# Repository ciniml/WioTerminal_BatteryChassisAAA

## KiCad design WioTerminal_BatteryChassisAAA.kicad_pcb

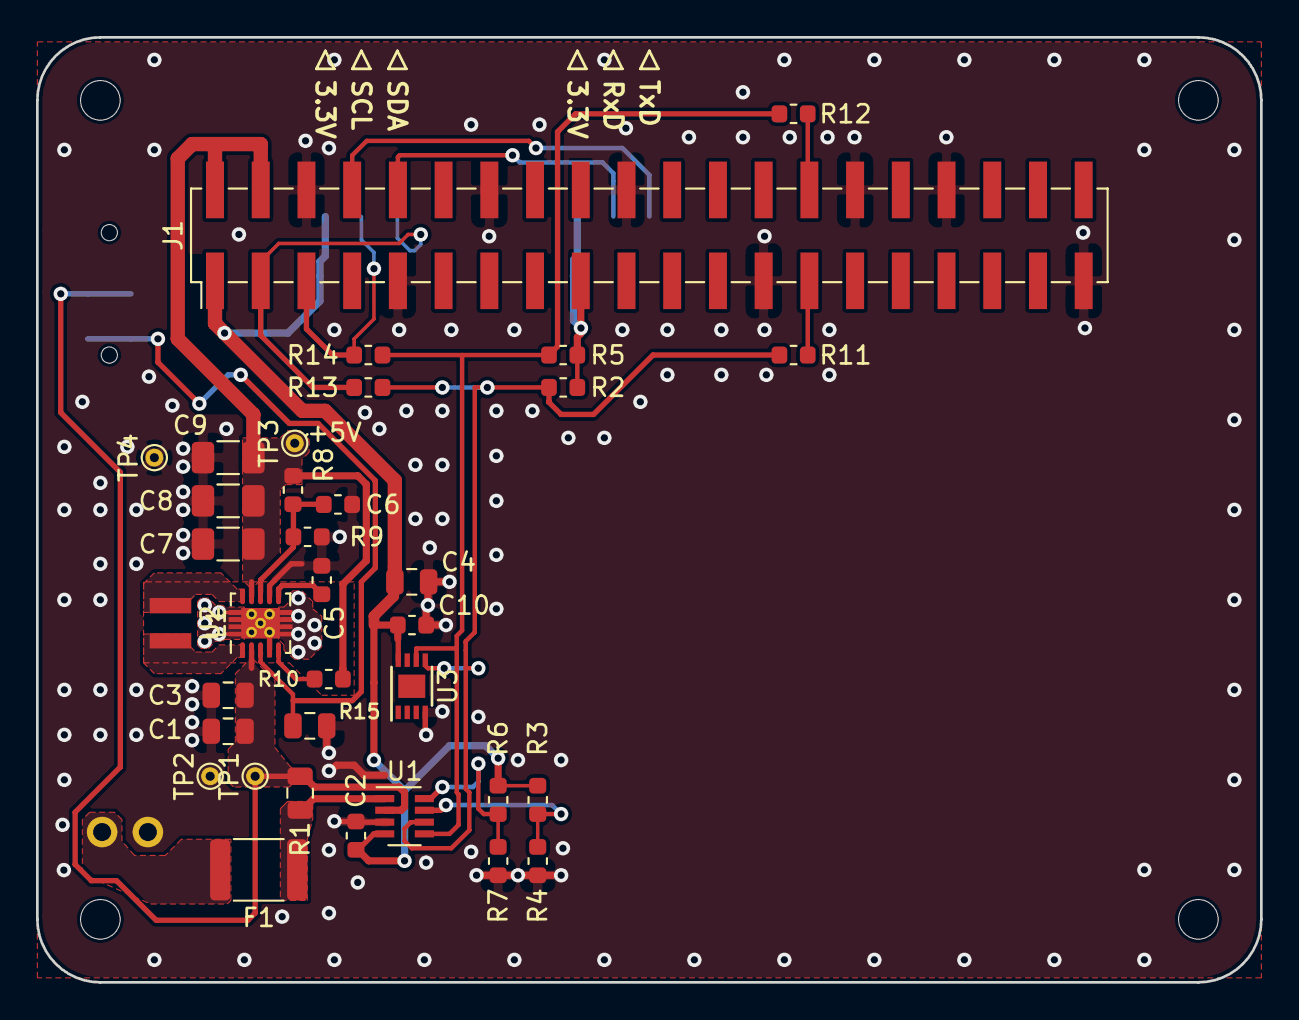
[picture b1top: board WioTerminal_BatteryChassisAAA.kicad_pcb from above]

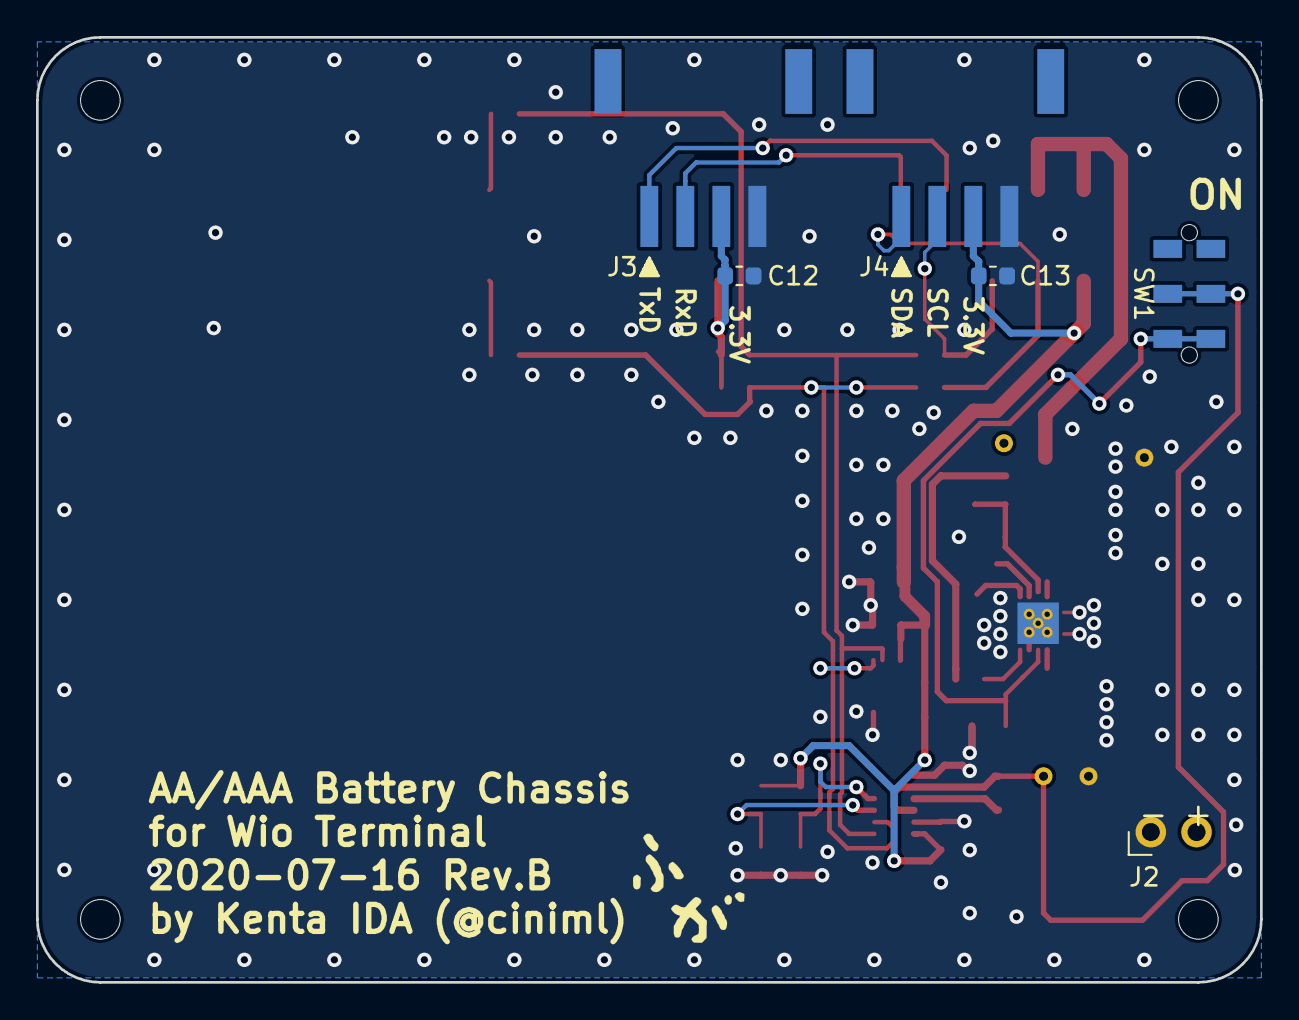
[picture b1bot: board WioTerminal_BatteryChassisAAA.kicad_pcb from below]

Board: 2 copper layers, 68.0 x 52.5 mm, 46 parts (7 on the bottom side), 22 nets.

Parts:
C1, C3, C4: 10u; C_0805_2012Metric
C2, C5, C10: 100n; C_0603_1608Metric
C6: 10p; C_0603_1608Metric
C7, C8, C9: 22u; C_1206_3216Metric
C12, C13: 1u; C_0603_1608Metric
F1: 1A; Fuse_1812_4532Metric
J1: Raspberry_Pi_2_3; PinHeader_2x20_P2.54mm_Vertical_SMD
J2: Ext. BAT; PinHeader_1x02_P2.54mm_Horizontal
J3, J4: GROVE; PHS-4AW
L1: 1u, 2.5A; 74438323010
LOGO1: Logo_Open_Hardware_Small; logo
MH1, MH2, MH3, MH4: Corner; MountingHole_2.2mm_M2_DIN965_Mask
R1: 0.04; R_0805_2012Metric
R2, R5: 4.7k; R_0603_1608Metric
R3, R6, R11, R12: 0; R_0603_1608Metric
R4, R7, R13, R14: DNP; R_0603_1608Metric
R8, R10: 1M; R_0603_1608Metric
R9: 111k; R_0603_1608Metric
R15: 100k; R_0805_2012Metric
SW1: JS102011JAQN
TP1: BAT; TestPoint_THTPad_D1.0mm_Drill0.5mm
TP2: BAT-GND; TestPoint_THTPad_D1.0mm_Drill0.5mm
TP3: +5V; TestPoint_THTPad_D1.0mm_Drill0.5mm
TP4: +5V-GND; TestPoint_THTPad_D1.0mm_Drill0.5mm
U1: INA219; SOT-23-8
U2: TPS63060; Texas_S-PWSON-N10_ThermalVias
U3: ATECC608A; DFN-8-1EP_3x2mm_P0.5mm_EP1.3x1.5mm

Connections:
+3V3: C2.1, C4.1, C10.1, C12.1, C13.1, J1.1, J1.17, J3.3, J4.3, R2.1, R3.1, R5.1, R6.1, U1.4, U3.8
+5V: C7.1, C8.1, C9.1, J1.2, J1.4, R8.1, R10.1, TP3.1, U2.9
/A0: R3.2, R4.1, U1.7
/A1: R6.2, R7.1, U1.8
/I2C1_SCL: J1.5, J4.2, R14.2
/I2C1_SDA: J1.3, J4.1, R13.2
/RXD: J1.10, J3.2
/SCL: R5.2, R12.1, R14.1, U1.5, U3.6
/SDA: R2.2, R11.1, R13.1, U1.6, U3.5
/TXD: J1.8, J3.1
GND: C1.2, C2.2, C3.2, C4.2, C5.2, C6.2, C7.2, C8.2, C9.2, C10.2, C12.2, C13.2, J1.6, J1.9, J1.14, J1.20, J1.25, J1.30, J1.34, J1.39, J2.2, J3.4, J4.4, R4.2, R7.2, R9.2, R15.1, TP2.1, TP4.1, U1.3, U2.4, U2.7, U2.11, U3.4
unnamed: C1.1, C3.1, R1.1, SW1.2, TP1.1, U1.2, U2.2
unnamed: C5.1, U2.6
unnamed: C6.1, R8.2, R9.1, U2.8
unnamed: F1.1, R1.2, U1.1
unnamed: F1.2, J2.1
unnamed: J1.27, R11.2
unnamed: J1.28, R12.2
unnamed: L1.1, U2.1
unnamed: L1.2, U2.10
unnamed: R10.2, U2.5
unnamed: R15.2, SW1.1, U2.3

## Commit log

2020-06-24 Revision A
2020-06-27 Add enclosure
2020-06-29 Slide cover enclosure (not good)
2020-07-12 Change enclosure slide shape
2020-07-12 Fix wrong INA-219 pin assignment
2020-07-15 Fix INA-219 connection
